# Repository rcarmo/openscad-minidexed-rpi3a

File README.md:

# MiniDexed RPI 3A Case

This is a case for a [MiniDexed] synthesizer built with a Raspberry Pi 3A, a DAC and a custom board for a MIDI IN TRS jack (schematic included in the `kicad-mini-in` folder--I ended up just using a protoboard, so there's no real PCB data for that).

This repository includes the `STL` files for the case (top, bottom and knob), as well as the [OpenSCAD](https://openscad.org) files for the case and all boards (some of which I modified from some of the excellent libraries I keep tabs on [here](https://taoofmac.com/space/apps/openscad)).

There is also an (incomplete) slanted/oblique version of the case, which I may or may not finish.

## MIDI IN Schematic

This is a pretty simple schematic, and I ended up just using a protoboard for it. The TRS jack is a 2.5mm MIDI IN jack, and other than the [`H11L1M`](https://www.onsemi.com/products/interfaces/high-performance-optocouplers/high-speed-logic-gate-optocouplers/h11l1m) optocoupler, everything else is just a few resistors and capacitors:

## Checklist

- [x] Check all screw hole sizes
- [x] Knob
- [x] Deeper top pattern (0.5mm)
- [x] LED hole
- [x] Wider SD card slot inset
- [x] MIDI TRS jack

## Printing Notes

Printed in PLA, 0.2mm layer height, 3 perimeters, 3 top/bottom layers. I used Sunlu PLA+ for the bottom half of the case and Eryone Galaxy Black for the top and knob.

You may want to print the top half of the case with a plain face, but I went for a little more texture (which may or may not work well depending on PLA and lighting). I recommend printing the flat face down, and using mouse ear brims to keep it from warping (although the supports will help with that, too).

[MiniDexed]: https://github.com/probonopd/MiniDexed

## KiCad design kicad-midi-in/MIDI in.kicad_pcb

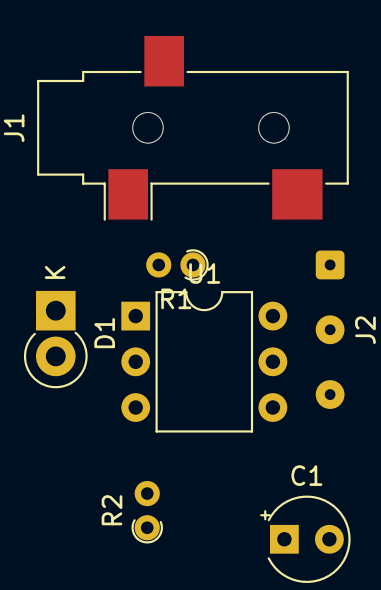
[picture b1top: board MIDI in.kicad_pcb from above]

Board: 2 copper layers, 7 parts (0 on the bottom side), 6 nets, no tracks yet.

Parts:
C1: 100nF/6.3V; CP_Radial_Tantal_D4.5mm_P2.50mm
D1: 1N4148; D_DO-41_SOD81_P2.54mm_Vertical_KathodeUp
J1: 3.5mm; Jack_3.5mm_CUI_SJ-3523-SMT_Horizontal
J2: Output; SolderWire-0.1sqmm_1x03_P3.6mm_D0.4mm_OD1mm
R1: 22O; R_Axial_DIN0204_L3.6mm_D1.6mm_P1.90mm_Vertical
R2: 1K; R_Axial_DIN0204_L3.6mm_D1.6mm_P1.90mm_Vertical
U1: H11L1M; DIP-6_W7.62mm

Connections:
+3V3: C1.1, J2.PI PIN 1 (Pin_1), R2.1, U1.6
GND: C1.2, J2.PI PIN 9 (Pin_3), U1.5
unnamed: D1.1 (K), R1.2, U1.1
unnamed: D1.2 (A), J1.T, U1.2
unnamed: J1.R, R1.1
unnamed: J2.PI PIN 10 (Pin_2), R2.2, U1.4

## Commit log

2024-01-13 initial import
